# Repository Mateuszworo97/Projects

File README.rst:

About
-----

.. raw:: html

   <div style="text-align: justify;">

   <p>
   <strong>Apiary Water Dispensing System</strong> —  This is a device design whose purpose is to automatically supply bee water from an underground tank.
   In hard-to-reach places and with limited access to fresh water.
   The system's task is also to display current data regarding time, temperature and light intensity on the display.
   The system will enable the pump to be turned on at a specific time for a specific period of time.
   </p>

   <p>
   In the future, this project will be extended with new functionalities.
   Currently, I am working on two versions of the system that will reduce the size of the PCB and the number of components used.
   </p>

   <ul>
     <li><strong>Version 1:</strong> Uses the same components as the current version but in a smaller layout.</li>
     <li><strong>Version 2:</strong> Introduces new components to reduce PCB size while keeping the system expandable.</li>
     <li><strong>Version 3:</strong> Adds wireless data transmission using <em>LORAWAN</em> technology and integration with cloud platforms such as <em>ThingsBoard</em> or <em>TTN (The Things Network)</em>.</li>
   </ul>
   
   <p>
   One version will use the same components as the current one, but will be smaller in size.
   The second version will allow include new components that will reduce the size of the PCB board, but won't limit possibility of expended the system in the future.
   The PCB board will contains derivations for additional components that can be added later.
   The third version will expand the funtionality of the system with wireless data transmission using LORAWAN technology.
   Target of the system is to send data to cloud platform such as THINGSBOARD or TTN (The Things Network).
   Definitely, such action will investigate natural environment around device and bees activity.
   Currently, the first of version system has contributed to better understanding of bees behavior in hard to reach places with limited access to fresh water.
   I think that the third version of the system will be a great tool for beekeepers to monitor the environment around the beehive and bees activity.
   Above all, the system will allow to achieve the significant level of automation and considerably contributed to increase the capacity and coverage of the lorawan Network.
   </p>

Operation
------------

The system measures time, temperature, humidity, light intensity, battery voltage, 
value and direction of battery current flow, power consumered and delivered to battery,
Voltage of photovoltaic panel, value of photovoltaic panel.
The data is shown on the display.
By default, the pump is turned on for 1 minute. Every hour.
Using push buttons, we can increase the pump activation time from 1 to 59 minutes.
Using the buttons, we can also change the time at which the alarm will turn on (pump on).
The next time the alarm will turn on will be increased by the hour value displayed on the display.
we can delay the pump activation value from 1 to 16 hours.

Development
------------

1. Simplification 
2. Adding an automatic and manual control system
3. Enriching the project with wireless data transmission using  LORAWAN technology
4. Desiging a much smaller PCB
5. Creating own MPPT board

Block Diagram
------------
.. image::  https://github.com/Mateuszworo97/Projects/blob/experiment/Embedded_projects/docs/images/blockDiagram.png
    :alt: Block Diagram
    :align: center

Visualization
------------
.. image::  https://github.com/Mateuszworo97/Projects/blob/experiment/Embedded_projects/docs/images/3D_visualization.PNG
    :alt: Visualization
    :align: center

.. image::  https://github.com/Mateuszworo97/Projects/blob/experiment/Embedded_projects/docs/images/routedPCBtracks.PNG
    :alt: Routed PCB tracks
    :align: center

Components
------------

Contains a list of components used to build the system

Refer to `docs/components.rst`.

Hardware
------------

Contains documentation of the sensors and components used.
-Diagram of the electronic system of the device.

Refer to `docs/hardware`.

Software
------------

-Diagram of the software nic system of the device.
Refer to `docs/software`.

License
------------

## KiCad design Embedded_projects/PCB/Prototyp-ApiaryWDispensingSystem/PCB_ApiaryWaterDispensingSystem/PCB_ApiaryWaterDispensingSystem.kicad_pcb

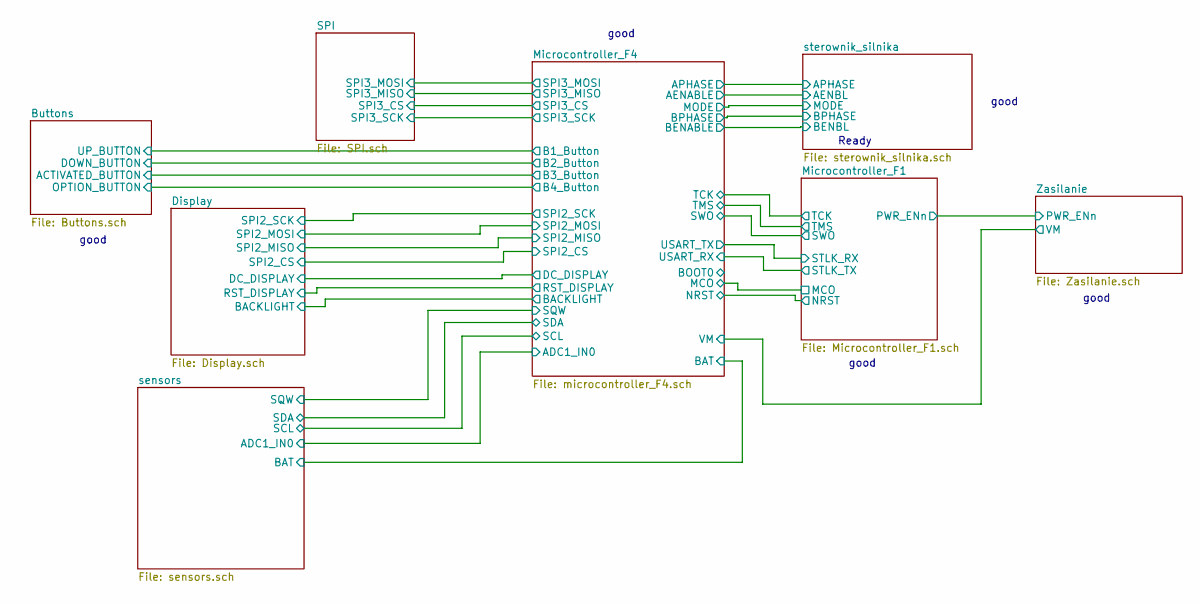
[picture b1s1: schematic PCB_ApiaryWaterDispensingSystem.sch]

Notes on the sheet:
Ready
good

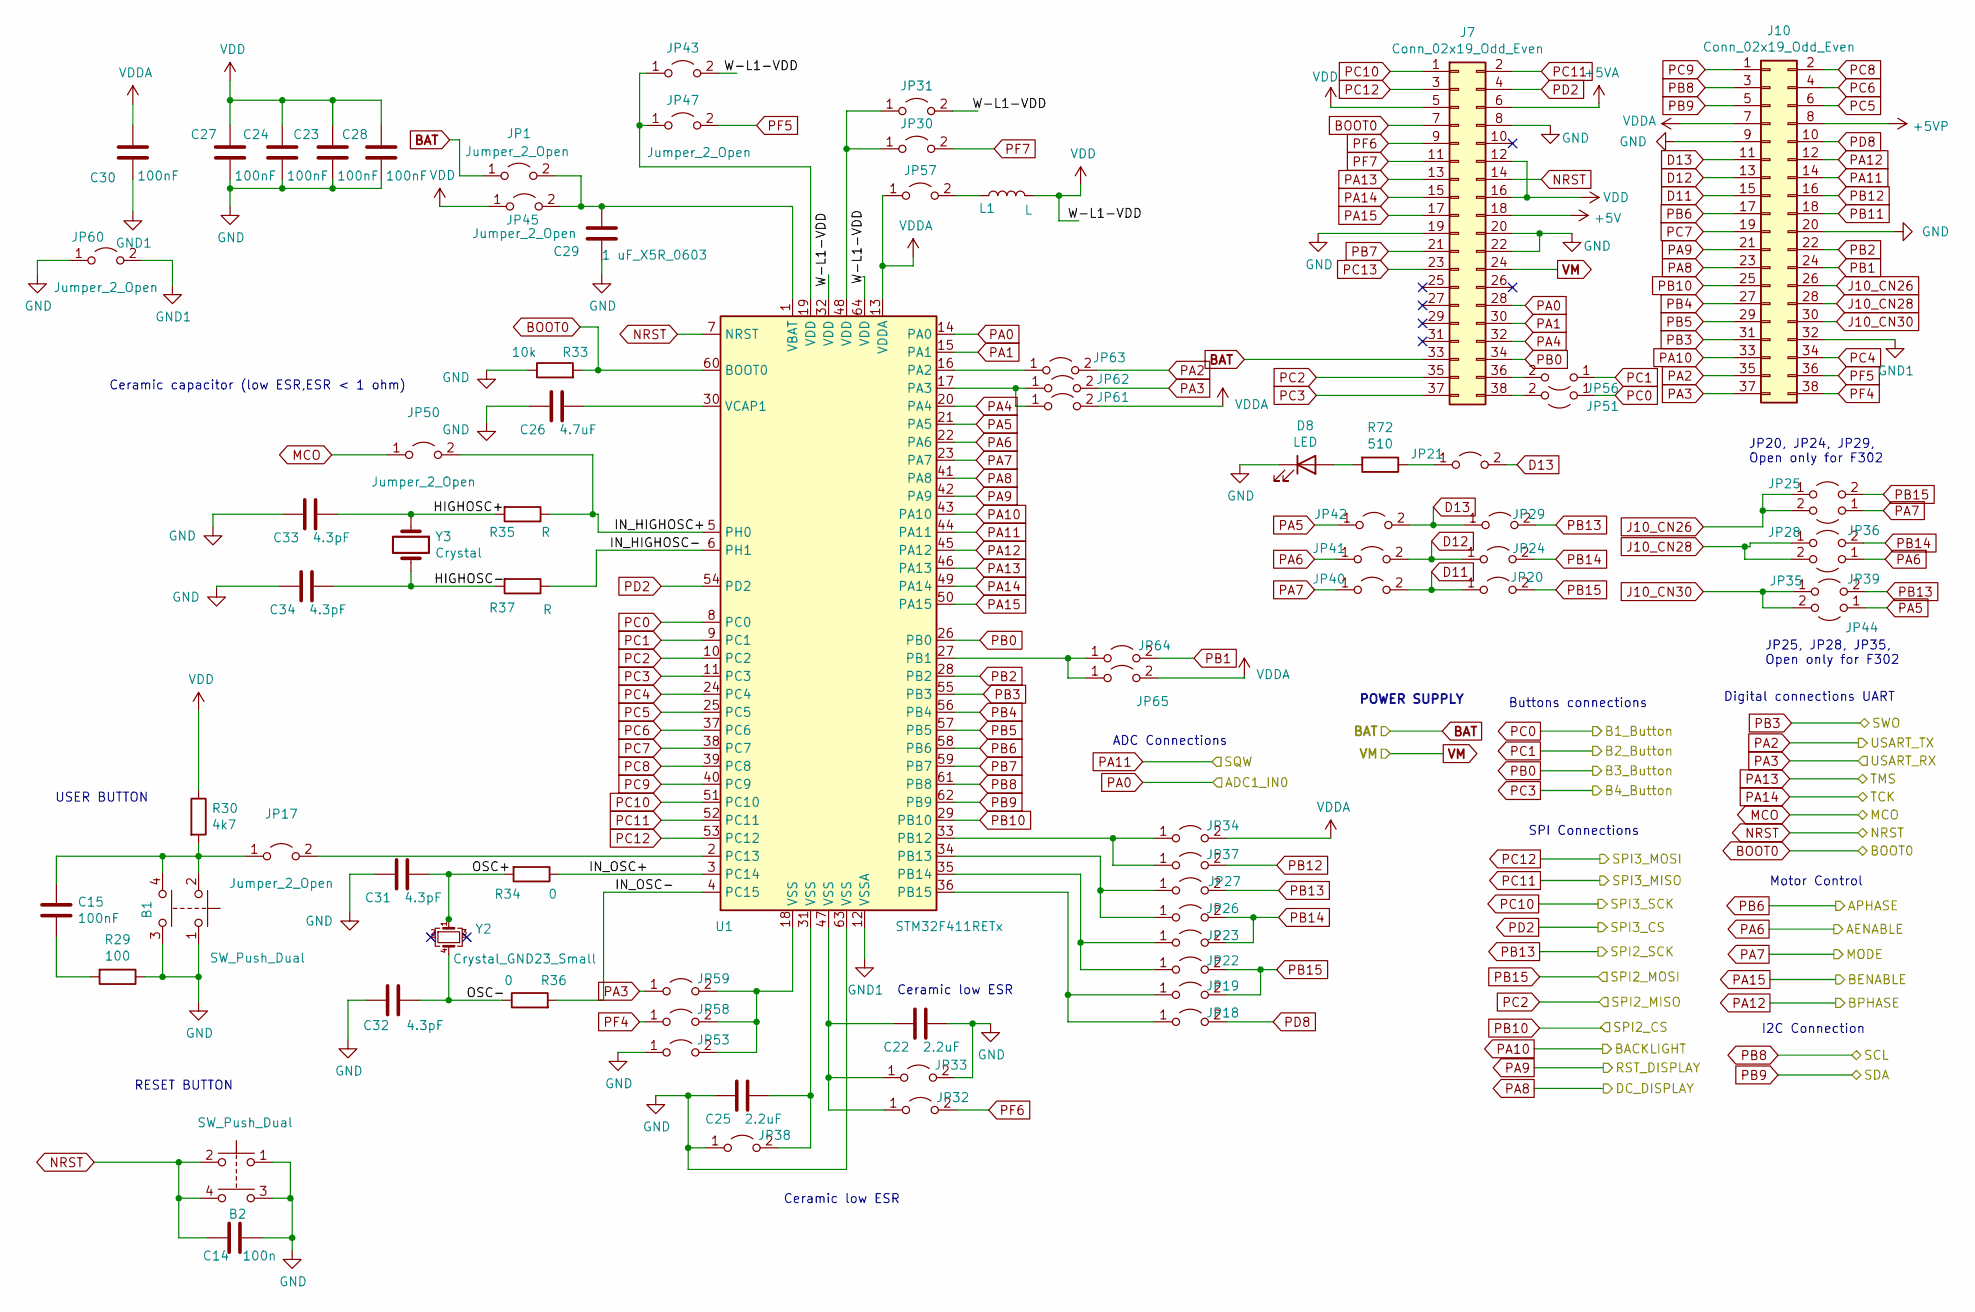
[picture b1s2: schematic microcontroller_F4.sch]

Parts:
B1, B2: SW_Push_Dual; SW_SPST_Omron_B3FS-100xP
C14: 100n; C_0603_1608Metric
C15, C23, C24, C27, C28, C30: 100nF; C_0603_1608Metric
C22, C25: 2.2uF; C_1206_3216Metric
C26: 4.7uF; C_0805_2012Metric
C29: 1 uF_X5R_0603; C_0603_1608Metric
C31, C32, C33, C34: 4.3pF; C_0603_1608Metric
D8: LED; LED_0805_2012Metric
J7, J10: Conn_02x19_Odd_Even; PinHeader_2x19_P2.54mm_Vertical
JP1, JP17, JP18, JP19, JP20, JP21, JP22, JP23, JP24, JP25, JP26, JP27, JP28, JP29, JP30, JP31, JP32, JP33, JP34, JP35, JP36, JP37, JP38, JP39, JP40, JP41, JP42, JP43, JP44, JP45, JP47, JP50, JP51, JP53, JP56, JP57, JP58, JP59, JP60, JP61, JP62, JP63, JP64, JP65: Jumper_2_Open; SolderJumper-2_P1.3mm_Open_TrianglePad1.0x1.5mm
L1: L; L_0603_1608Metric
R29: 100; R_0603_1608Metric
R30: 4k7; R_0603_1608Metric
R33: 10k; R_0603_1608Metric
R34, R36: 0; R_0603_1608Metric
R35, R37: R; R_0603_1608Metric
R72: 510; R_0603_1608Metric
U1: STM32F411RETx; LQFP-64_10x10mm_P0.5mm
Y2: Crystal_GND23_Small; ABS25-32768KHZ-6-T_Abracon
Y3: Crystal; Resonator-2Pin_W8.0mm_H3.5mm

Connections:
+5V: J7.18; also elsewhere on the board
+5VA: J7.6; also elsewhere on the board
+5VP: J10.8; also elsewhere on the board
/Microcontroller_F4/HIGHOSC+: C33.1, R35.2, Y3.1
/Microcontroller_F4/HIGHOSC-: C34.1, R37.2, Y3.2
/Microcontroller_F4/IN_HIGHOSC+: JP50.2 (B), R35.1, U1.5 (PH0)
/Microcontroller_F4/IN_HIGHOSC-: R37.1, U1.6 (PH1)
/Microcontroller_F4/IN_OSC+: R34.1, U1.3 (PC14)
/Microcontroller_F4/IN_OSC-: R36.2, U1.4 (PC15)
/Microcontroller_F4/OSC+: C31.1, R34.2, Y2.1
/Microcontroller_F4/OSC-: C32.1, R36.1, Y2.4
ADC1_IN0: J7.28, U1.14 (PA0); also elsewhere on the board
AENABLE: JP39.1 (A), JP41.1 (A), U1.22 (PA6); also elsewhere on the board
APHASE: J10.17, U1.58 (PB6); also elsewhere on the board
BAT: J7.33, JP1.1 (A); also elsewhere on the board
BENABLE: J7.17, U1.50 (PA15); also elsewhere on the board
BOOT0: J7.7, R33.2, U1.60 (BOOT0); also elsewhere on the board
BPHASE: J10.12, U1.45 (PA12); also elsewhere on the board
Backlight: J10.33, U1.43 (PA10); also elsewhere on the board
CLK: J7.1, U1.51 (PC10); also elsewhere on the board
CMD: J7.3, U1.53 (PC12); also elsewhere on the board
D11: J10.15, JP20.1 (A), JP40.2 (B)
D12: J10.13, JP24.1 (A), JP41.2 (B)
D13: J10.11, JP21.2 (B), JP29.1 (A), JP42.2 (B)
DAT0: J7.2, U1.52 (PC11); also elsewhere on the board
DAT3: J7.4, U1.54 (PD2); also elsewhere on the board
DC_DISPLAY: J10.23, U1.41 (PA8); also elsewhere on the board
GND1: C30.1, J10.32, JP60.2 (B), U1.12 (VSSA)
J10_CN26: J10.26, JP25.1 (A), JP36.2 (B)
J10_CN28: J10.28, JP28.1 (A), JP39.2 (B)
J10_CN30: J10.30, JP35.1 (A), JP44.2 (B)
MCO: JP50.1 (A); also elsewhere on the board
MODE: JP36.1 (A), JP40.1 (A), U1.23 (PA7); also elsewhere on the board
NRST: B2.2, B2.4, C14.2, J7.14, U1.7 (NRST); also elsewhere on the board
unnamed: B1.2, B1.4, C15.1, JP17.1 (A), R30.2
unnamed: C15.2, R29.2
unnamed: C22.2, JP32.1 (A), JP33.1 (A), U1.47 (VSS)
unnamed: C25.1, JP38.2 (B), U1.31 (VSS)
unnamed: C26.1, U1.30 (VCAP1)
unnamed: C29.2, JP1.2 (B), JP45.2 (B), U1.1 (VBAT)
unnamed: D8.2 (A), R72.2
unnamed: J7.36, JP56.2 (B)
unnamed: J7.38, JP51.2 (B)
unnamed: JP17.2 (B), U1.2 (PC13)
unnamed: JP18.1 (A), JP19.1 (A), U1.36 (PB15)
unnamed: JP21.1 (A), R72.1
unnamed: JP22.1 (A), JP23.1 (A), U1.35 (PB14)
unnamed: JP26.1 (A), JP27.1 (A), U1.34 (PB13)
unnamed: JP30.1 (A), JP31.1 (A), U1.48 (VDD)
unnamed: JP34.1 (A), JP37.1 (A), U1.33 (PB12)
unnamed: JP43.1 (A), JP47.1 (A), U1.19 (VDD)
unnamed: JP53.2 (B), JP58.2 (B), JP59.2 (B), U1.18 (VSS)
unnamed: JP57.2 (B), L1.1
unnamed: JP61.1 (A), JP62.1 (A), U1.17 (PA3)
unnamed: JP63.1 (A), U1.16 (PA2)
unnamed: JP64.1 (A), JP65.1 (A), U1.27 (PB1)
PA1: J7.30, U1.15 (PA1)
PA2: J10.35, JP63.2 (B); also elsewhere on the board
PA3: J10.37, JP59.1 (A), JP62.2 (B); also elsewhere on the board
PA4: J7.32, U1.20 (PA4)
PA5: JP42.1 (A), JP44.1 (A), U1.21 (PA5)
PA9: J10.21, U1.42 (PA9); also elsewhere on the board
PA11: J10.14, U1.44 (PA11); also elsewhere on the board
PA13: J7.13, U1.46 (PA13); also elsewhere on the board
PA14: J7.15, U1.49 (PA14); also elsewhere on the board
PB0: J7.34, U1.26 (PB0); also elsewhere on the board
PB1: J10.24, JP64.2 (B)
PB2: J10.22, U1.28 (PB2)
PB3: J10.31, U1.55 (PB3); also elsewhere on the board
PB4: J10.27, U1.56 (PB4)
PB5: J10.29, U1.57 (PB5)
PB7: J7.21, U1.59 (PB7)
PB8: J10.3, U1.61 (PB8); also elsewhere on the board
PB9: J10.5, U1.62 (PB9); also elsewhere on the board
PB10: J10.25, U1.29 (PB10); also elsewhere on the board
PB12: J10.16, JP37.2 (B)
PB13: JP27.2 (B), JP29.2 (B), JP35.2 (B); also elsewhere on the board
PB14: JP23.2 (B), JP24.2 (B), JP26.2 (B), JP28.2 (B)
PB15: JP19.2 (B), JP20.2 (B), JP22.2 (B), JP25.2 (B); also elsewhere on the board
PC0: JP51.1 (A), U1.8 (PC0); also elsewhere on the board
PC1: JP56.1 (A), U1.9 (PC1); also elsewhere on the board
PC2: J7.35, U1.10 (PC2)
PC3: J7.37, U1.11 (PC3); also elsewhere on the board
PC4: J10.34, U1.24 (PC4)
PC5: J10.6, U1.25 (PC5)
PC6: J10.4, U1.37 (PC6)
PC7: J10.19, U1.38 (PC7)
PC8: J10.2, U1.39 (PC8)
PC9: J10.1, U1.40 (PC9)
PD8: J10.10, JP18.2 (B)
PF4: J10.38, JP58.1 (A)
PF5: J10.36, JP47.2 (B)
PF6: J7.9, JP32.2 (B)
PF7: J7.11, JP30.2 (B)
VDD: C23.2, C24.2, C27.2, C28.2, J7.5, J7.12, J7.16, JP31.2 (B), JP43.2 (B), JP45.1 (A), L1.2, R30.1, U1.32 (VDD), U1.64 (VDD); also elsewhere on the board
VDDA: C30.2, J10.7, JP34.2 (B), JP57.1 (A), JP61.2 (B), JP65.2 (B), U1.13 (VDDA)
VM: J7.24; also elsewhere on the board

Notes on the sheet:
Ceramic capacitor (low ESR,ESR < 1 ohm)
Ceramic low ESR
RESET BUTTON
USER BUTTON
Buttons connections
Digital connections UART
SPI Connections
Motor Control
I2C Connection
JP25, JP28, JP35, Open only for F302
JP20, JP24, JP29, Open only for F302
POWER SUPPLY
ADC Connections

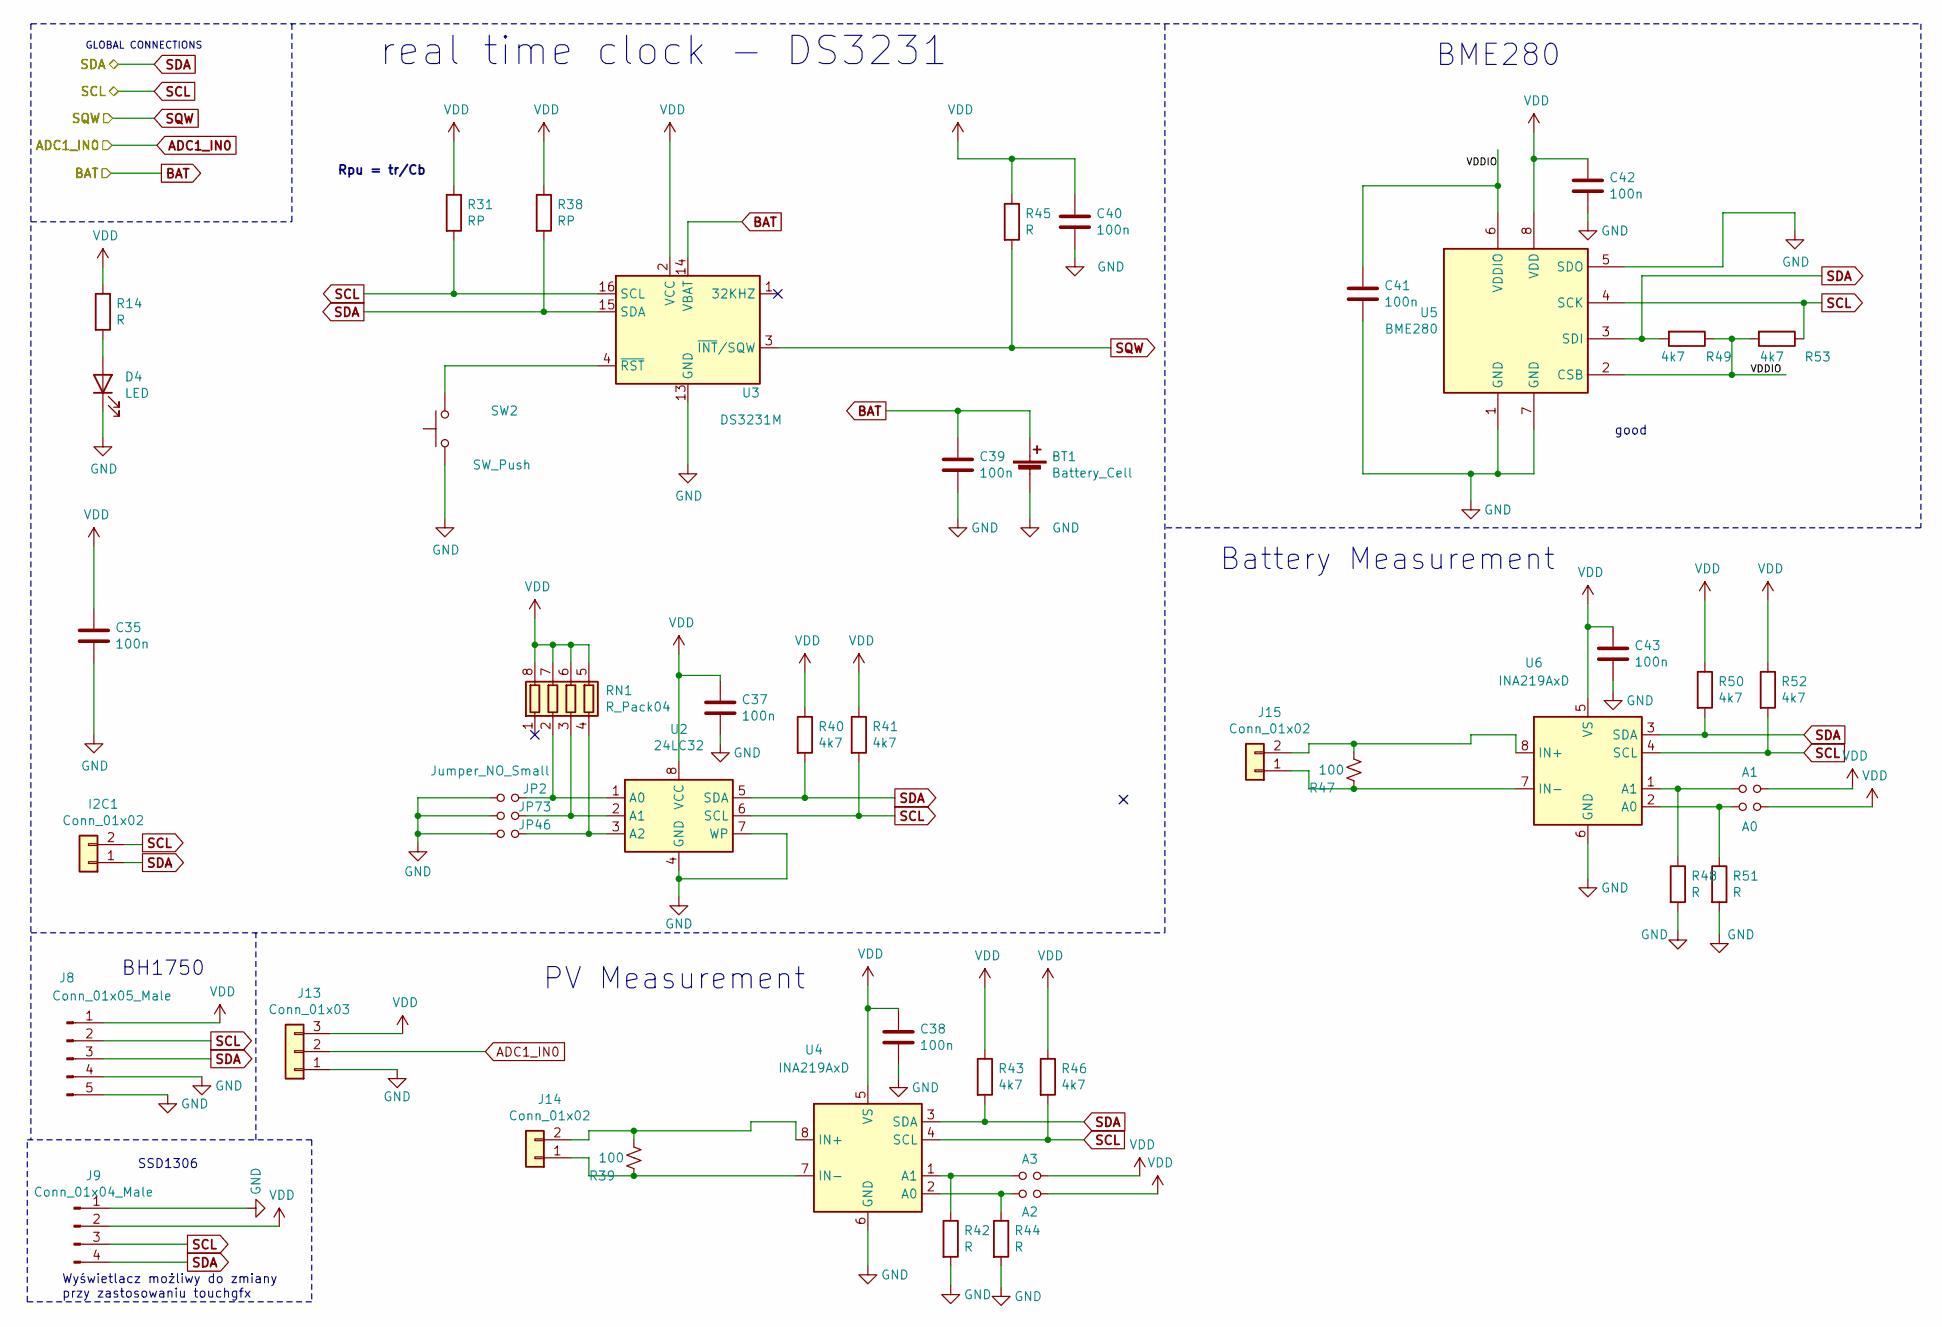
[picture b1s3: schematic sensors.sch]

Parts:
A0, A1, A2, A3: Jumper_NO_Small; SolderJumper-2_P1.3mm_Open_TrianglePad1.0x1.5mm
BT1: Battery_Cell; BatteryHolder_Keystone_107_1x23mm
C35, C37, C38, C39, C40, C41, C42, C43: 100n; C_0603_1608Metric
D4: LED; D_0805_2012Metric
I2C1: Conn_01x02; PinSocket_1x02_P2.54mm_Vertical
J8: Conn_01x05_Male; PinSocket_1x05_P1.27mm_Vertical
J9: Conn_01x04_Male; PinSocket_1x04_P2.54mm_Vertical
J13: Conn_01x03; TerminalBlock_TE_282834-3_1x03_P2.54mm_Horizontal
J14, J15: Conn_01x02; TerminalBlock_4Ucon_1x02_P3.50mm_Horizontal
JP2, JP46, JP73: Jumper_NO_Small; SolderJumper-2_P1.3mm_Open_TrianglePad1.0x1.5mm
R14, R42, R44, R45, R48, R51: R; R_0603_1608Metric
R31, R38: RP; R_0603_1608Metric
R39, R47: 100; R_2512_6332Metric
R40, R41, R43, R46, R49, R50, R52, R53: 4k7; R_0603_1608Metric
RN1: R_Pack04; R_Array_Convex_4x0603
SW2: SW_Push; SW_Push_1P1T_NO_6x6mm_H9.5mm
U2: 24LC32
U3: DS3231M; SOIC-16W_7.5x10.3mm_P1.27mm
U4, U6: INA219AxD; SOIC-8_3.9x4.9mm_P1.27mm
U5: BME280; Bosch_LGA-8_2.5x2.5mm_P0.65mm_ClockwisePinNumbering

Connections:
/sensors/VDDIO: C41.1, R49.1, R53.2, U5.2 (CSB), U5.6 (VDDIO)
ADC1_IN0: J13.2; also elsewhere on the board
BAT: BT1.1 (+), C39.1, U3.14 (VBAT); also elsewhere on the board
unnamed: A0.1, R51.1, U6.2 (A0)
unnamed: A1.1, R48.1, U6.1 (A1)
unnamed: A2.1, R44.1, U4.2 (A0)
unnamed: A3.1, R42.1, U4.1 (A1)
unnamed: D4.2 (A), R14.2
unnamed: J14.1, R39.1, U4.7 (IN-)
unnamed: J14.2, R39.2, U4.8 (IN+)
unnamed: J15.1, R47.1, U6.7 (IN-)
unnamed: J15.2, R47.2, U6.8 (IN+)
unnamed: JP2.2, RN1.2 (R2.1), U2.1 (A0)
unnamed: JP46.2, RN1.4 (R4.1), U2.3 (A2)
unnamed: JP73.2, RN1.3 (R3.1), U2.2 (A1)
unnamed: SW2.2, U3.4 (~RST)
PA11: R45.2, U3.3 (~INT~/SQW); also elsewhere on the board
PB8: I2C1.2, J8.2, J9.3, R31.2, R41.2, R46.2, R52.2, R53.1, U2.6 (SCL), U3.16 (SCL), U4.4 (SCL), U5.4 (SCK), U6.4 (SCL); also elsewhere on the board
PB9: I2C1.1, J8.3, J9.4, R38.2, R40.2, R43.2, R49.2, R50.2, U2.5 (SDA), U3.15 (SDA), U4.3 (SDA), U5.3 (SDI), U6.3 (SDA); also elsewhere on the board
VDD: A0.2, A1.2, A2.2, A3.2, C35.1, C37.1, C38.1, C40.1, C42.1, C43.1, J8.1, J9.2, J13.3, R14.1, R31.1, R38.1, R40.1, R41.1, R43.1, R45.1, R46.1, R50.1, R52.1, RN1.5 (R4.2), RN1.6 (R3.2), RN1.7 (R2.2), RN1.8 (R1.2), U2.8 (VCC), U3.2 (VCC), U4.5 (VS), U5.8 (VDD), U6.5 (VS); also elsewhere on the board

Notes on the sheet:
real time clock - DS3231
Rpu = tr/Cb
BME280
GLOBAL CONNECTIONS
BH1750
Battery Measurement
PV Measurement
SSD1306
Wyświetlacz możliwy do zmiany przy zastosowaniu touchgfx
good

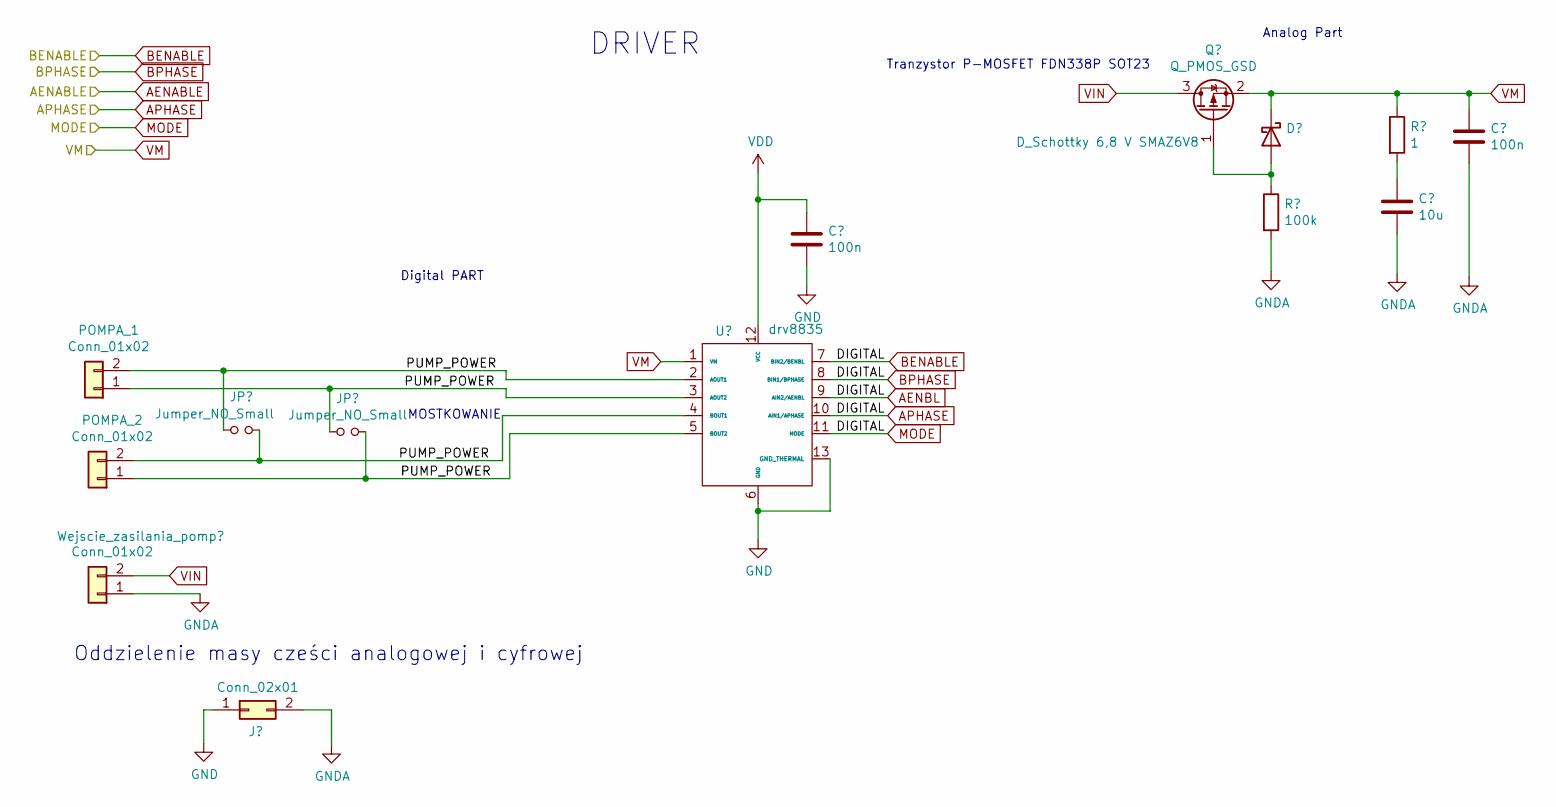
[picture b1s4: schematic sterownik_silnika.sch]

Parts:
POMPA_1, POMPA_2: Conn_01x02; TerminalBlock_TE_282834-2_1x02_P2.54mm_Horizontal

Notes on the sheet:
DRIVER
MOSTKOWANIE
Oddzielenie masy cześci analogowej i cyfrowej
Digital PART
Analog Part
Tranzystor P-MOSFET FDN338P SOT23

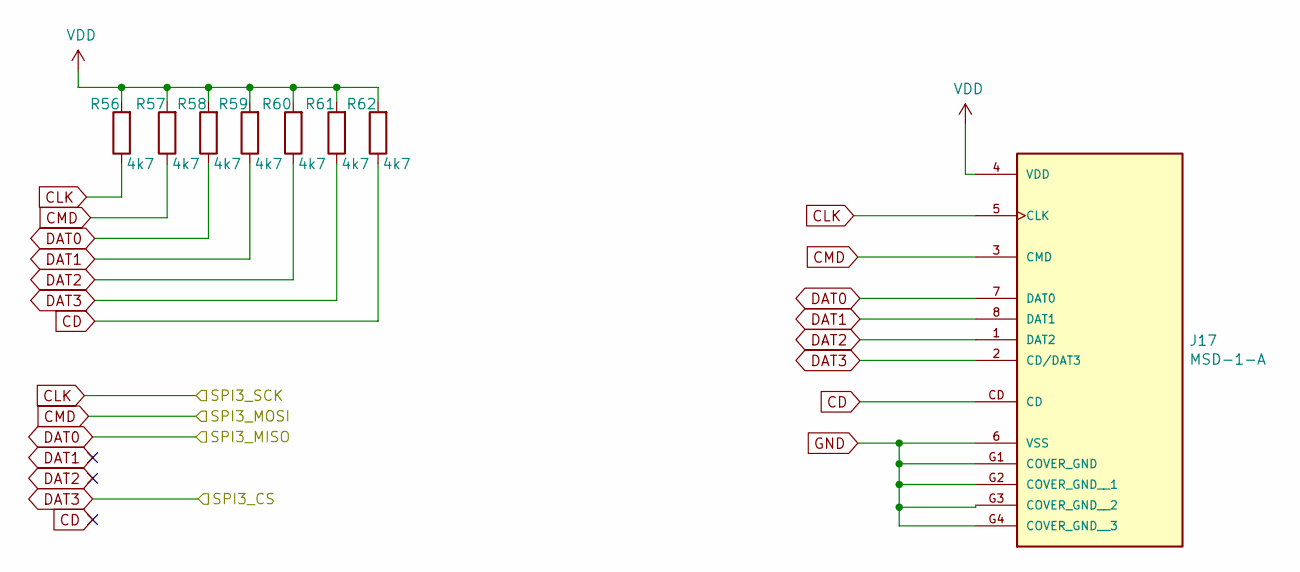
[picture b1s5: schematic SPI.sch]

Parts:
J17: MSD-1-A; CUI_MSD-1-A; PARTREV 1.0
R56, R57, R58, R59, R60, R61, R62: 4k7; R_0603_1608Metric

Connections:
CD: J17.CD, R62.1
CLK: J17.5 (CLK), R56.1; also elsewhere on the board
CMD: J17.3 (CMD), R57.1; also elsewhere on the board
DAT0: J17.7 (DAT0), R58.1; also elsewhere on the board
DAT1: J17.8 (DAT1), R59.1
DAT2: J17.1 (DAT2), R60.1
DAT3: J17.2 (CD/DAT3), R61.1; also elsewhere on the board
VDD: J17.4 (VDD), R56.2, R57.2, R58.2, R59.2, R60.2, R61.2, R62.2; also elsewhere on the board

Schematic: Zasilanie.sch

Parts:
C16, C17: 10uF(25V); CP_EIA-6032-15_Kemet-U
C18: 1uF_X5R_0603; C_0603_1608Metric
C19: 100nF; C_0603_1608Metric
C20: 100n; C_0603_1608Metric
C21: 1uF_X5R; C_0603_1608Metric
J5: Conn_01x03_Male; PinHeader_1x03_P2.54mm_Vertical
J6: Conn_02x01; PinHeader_1x02_P2.54mm_Vertical
R28: 4k7; R_0603_1608Metric
R32: 4k7

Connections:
+5V: C20.1, C21.1, J5.2, R32.1; also elsewhere on the board
+5VA: J5.1; also elsewhere on the board
+5VP: R28.1; also elsewhere on the board
unnamed 52: C17.1; also elsewhere on the board
unnamed 53: C18.1, C19.1; also elsewhere on the board
unnamed 70: R32.2; also elsewhere on the board
unnamed 79: J5.3; also elsewhere on the board
PWR_ENn: R28.2; also elsewhere on the board
VDD: J6.2; also elsewhere on the board
VM: C16.1; also elsewhere on the board

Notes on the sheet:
good

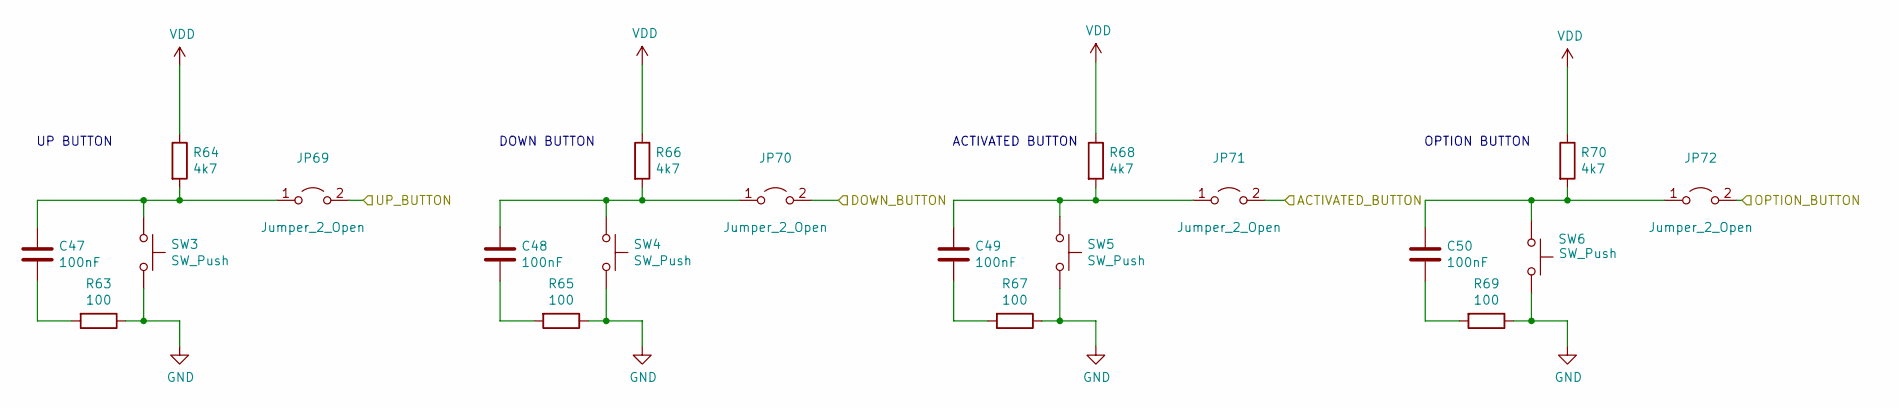
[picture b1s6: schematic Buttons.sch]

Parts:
C47, C48, C49, C50: 100nF; C_0603_1608Metric
JP69, JP70, JP71, JP72: Jumper_2_Open; SolderJumper-2_P1.3mm_Open_TrianglePad1.0x1.5mm
R63, R65, R67, R69: 100; R_0603_1608Metric
R64, R66, R68, R70: 4k7; R_0603_1608Metric
SW3, SW4, SW5, SW6: SW_Push; SW_PUSH-12mm

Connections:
unnamed: C47.1, JP69.1 (A), R64.2, SW3.1
unnamed: C47.2, R63.2
unnamed: C48.1, JP70.1 (A), R66.2, SW4.1
unnamed: C48.2, R65.2
unnamed: C49.1, JP71.1 (A), R68.2, SW5.1
unnamed: C49.2, R67.2
unnamed: C50.1, JP72.1 (A), R70.2, SW6.1
unnamed: C50.2, R69.2
PB0: JP71.2 (B); also elsewhere on the board
PC0: JP69.2 (B); also elsewhere on the board
PC1: JP70.2 (B); also elsewhere on the board
PC3: JP72.2 (B); also elsewhere on the board
VDD: R64.1, R66.1, R68.1, R70.1; also elsewhere on the board

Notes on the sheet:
UP BUTTON
DOWN BUTTON
ACTIVATED BUTTON
OPTION BUTTON

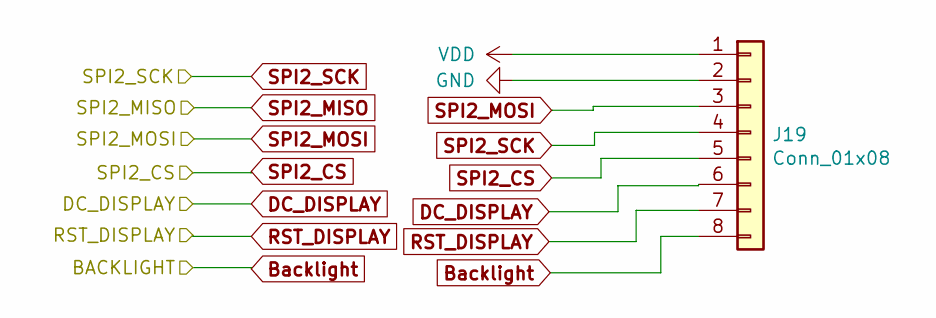
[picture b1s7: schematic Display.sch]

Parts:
J19: Conn_01x08; PinSocket_1x08_P2.54mm_Vertical

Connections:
Backlight: J19.8; also elsewhere on the board
DC_DISPLAY: J19.6; also elsewhere on the board
PA9: J19.7; also elsewhere on the board
PB10: J19.5; also elsewhere on the board
PB13: J19.4; also elsewhere on the board
PB15: J19.3; also elsewhere on the board
VDD: J19.1; also elsewhere on the board

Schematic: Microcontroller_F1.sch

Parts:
C1, C4, C5, C6, C7, C11, C12: 100n; C_0603_1608Metric
C2, C13: 1uF_X5R_0603; C_0603_1608Metric
C3, C8, C10: 20pF; C_0603_1608Metric
C9: 10nF_X7R; C_0603_1608Metric
D1, D2, D3: BAT60A; D_SOD-323
J1, J3, J11, J12: Conn_02x01; PinHeader_1x02_P2.54mm_Vertical
J2: Conn_01x04; PinHeader_1x04_P2.54mm_Vertical
J4: Conn_01x06; PinHeader_1x06_P2.54mm_Vertical
JP3, JP4, JP5, JP6, JP7, JP8, JP9, JP10, JP11, JP12, JP13, JP14, JP15, JP16: Jumper_2_Open; SolderJumper-2_P1.3mm_Open_TrianglePad1.0x1.5mm
R1, R2, R3, R12: 10k; R_0603_1608Metric
R4, R23, R27: 4k7; R_0603_1608Metric
R5, R8, R13, R22: 22; R_0603_1608Metric
R6, R15: 100k; R_0603_1608Metric
R7: 2k7; R_0603_1608Metric
R9, R11, R19, R20, R21, R25: 100; R_0603_1608Metric
R10: 36k; R_0603_1608Metric
R16: 1k5; R_0603_1608Metric
R17, R18: 0; R_0603_1608Metric
R24: 100; C_0603_1608Metric
R26: [N/A]; R_0603_1608Metric
X1: Crystal; Resonator-2Pin_W8.0mm_H3.5mm

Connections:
+5VA: D3.2 (A), R7.2; also elsewhere on the board
+5VP: D2.2 (A), R12.2; also elsewhere on the board
/Microcontroller_F1/OSC+: C3.2, X1.1; also elsewhere on the board
/Microcontroller_F1/OSC-: C8.1, X1.2; also elsewhere on the board
AIN_1: R9.1, R23.2, R27.2; also elsewhere on the board
BOOT0: R6.1; also elsewhere on the board
LED_STLINK: R20.1, R21.1; also elsewhere on the board
MCO: JP16.2 (B); also elsewhere on the board
NRST: JP12.2 (B); also elsewhere on the board
unnamed 48: C2.1, C5.1, D2.1 (K), D3.1 (K); also elsewhere on the board
unnamed 49: C9.1; also elsewhere on the board
unnamed: C10.1, JP16.1 (A), R25.1
unnamed: D1.1 (K), R9.2
unnamed: J2.1, JP3.2 (B), JP4.1 (A)
unnamed: J2.2, JP5.2 (B), JP6.1 (A)
unnamed: J2.3, JP7.2 (B), JP8.1 (A)
unnamed: J2.4, JP9.2 (B), JP10.1 (A)
unnamed: J4.4, R8.2
unnamed: J4.5, R13.2
unnamed: J4.6, R22.2
unnamed 86: R18.2; also elsewhere on the board
unnamed 87: R16.2, R17.2; also elsewhere on the board
unnamed 88: R15.2; also elsewhere on the board
unnamed 105: R21.2; also elsewhere on the board
unnamed 106: R20.2; also elsewhere on the board
unnamed 107: R19.1; also elsewhere on the board
unnamed 108: R10.2, R11.1, R12.1; also elsewhere on the board
unnamed 109: R16.1; also elsewhere on the board
unnamed 110: R2.2; also elsewhere on the board
unnamed 111: R3.2; also elsewhere on the board
unnamed 112: R25.2; also elsewhere on the board
PA2: JP13.2 (B); also elsewhere on the board
PA3: JP14.2 (B); also elsewhere on the board
PA13: JP9.1 (A); also elsewhere on the board
PA14: JP5.1 (A); also elsewhere on the board
PB3: JP15.2 (B); also elsewhere on the board
PWR_EXT: J1.2, R4.2, R7.1; also elsewhere on the board
STM_JTCK: JP6.2 (B); also elsewhere on the board
STM_JTMS: JP10.2 (B); also elsewhere on the board
STM_RST: C6.1, JP11.1 (A); also elsewhere on the board
ST_LINK_RX: J3.2, JP13.1 (A); also elsewhere on the board
ST_LINK_TX: J3.1, JP14.1 (A); also elsewhere on the board
T_JTCK: JP3.1 (A), R5.1; also elsewhere on the board
T_JTMS: JP7.1 (A), R8.1, R24.1; also elsewhere on the board
T_NRST: JP12.1 (A), R13.1; also elsewhere on the board
T_SWDIO_IN: R24.2; also elsewhere on the board
T_SWO: JP15.1 (A), R22.1; also elsewhere on the board
USB_DM: R17.1; also elsewhere on the board
USB_DP: R18.1; also elsewhere on the board
USB_RENUMn: R11.2; also elsewhere on the board

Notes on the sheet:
RESERVED
DEFAULT
JUMPERS ON --> NUCLEO Selected
JUMPERS OFF --> ST-LINK Selected
USB ST-Link
PINY HIERARCHICZNE
PWR
good
Wired on Solder Side

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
